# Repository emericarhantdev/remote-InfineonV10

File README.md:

# ECAD-TEMPLATE
Template for creating a new electronic design project. Automatically add gitignore and submodule library

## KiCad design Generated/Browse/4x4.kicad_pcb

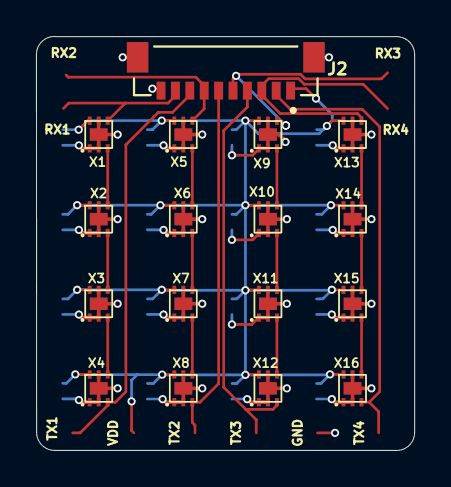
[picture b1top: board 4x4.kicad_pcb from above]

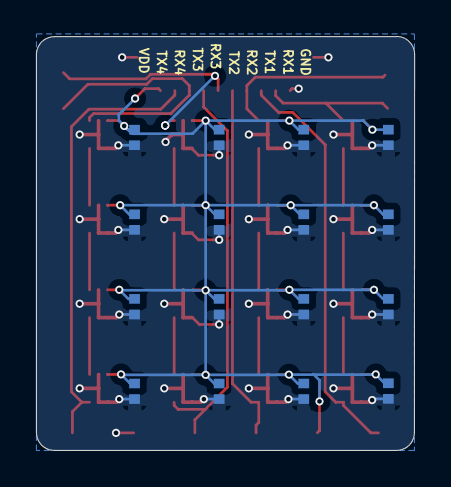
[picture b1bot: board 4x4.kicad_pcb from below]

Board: 2 copper layers, 21.0 x 23.0 mm, 33 parts (16 on the bottom side), 22 nets.

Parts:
CC_1, CC_2, CC_3, CC_4, CC_5, CC_6, CC_7, CC_8, CC_9, CC_10, CC_11, CC_12, CC_13, CC_14, CC_15, CC_16: C0402-CAPC1005X22N
J2: Amphenol-ICC_Minitek-08_10P
X1, X2, X3, X4, X5, X6, X7, X8, X9, X10, X11, X12, X13, X14, X15, X16: TLI493D-x4D7_R7_R1103_V3

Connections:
/Sensor Group/RX1: J2.9, X1.4 (TX)
/Sensor Group/RX2: J2.7, X5.4 (TX)
/Sensor Group/RX3: J2.5, X9.4 (TX)
/Sensor Group/RX4: J2.3, X13.4 (TX)
/Sensor Group/TX1: J2.8, X4.3 (RX)
/Sensor Group/TX2: J2.6, X8.3 (RX)
/Sensor Group/TX3: J2.4, X12.3 (RX)
/Sensor Group/TX4: J2.2, X16.3 (RX)
GND: CC_1.2, CC_2.2, CC_3.2, CC_4.2, CC_5.2, CC_6.2, CC_7.2, CC_8.2, CC_9.2, CC_10.2, CC_11.2, CC_12.2, CC_13.2, CC_14.2, CC_15.2, CC_16.2, J2.10, J2.S1 (SHIELD), J2.S2 (SHIELD__1), X1.1 (GND), X1.2 (NC), X1.5 (NC), X1.EP (NC), X2.1 (GND), X2.2 (NC), X2.5 (NC), X2.EP (NC), X3.1 (GND), X3.2 (NC), X3.5 (NC), X3.EP (NC), X4.1 (GND), X4.2 (NC), X4.5 (NC), X4.EP (NC), X5.1 (GND), X5.2 (NC), X5.5 (NC), X5.EP (NC), X6.1 (GND), X6.2 (NC), X6.5 (NC), X6.EP (NC), X7.1 (GND), X7.2 (NC), X7.5 (NC), X7.EP (NC), X8.1 (GND), X8.2 (NC), X8.5 (NC), X8.EP (NC), X9.1 (GND), X9.2 (NC), X9.5 (NC), X9.EP (NC), X10.1 (GND), X10.2 (NC), X10.5 (NC), X10.EP (NC), X11.1 (GND), X11.2 (NC), X11.5 (NC), X11.EP (NC), X12.1 (GND), X12.2 (NC), X12.5 (NC), X12.EP (NC), X13.1 (GND), X13.2 (NC), X13.5 (NC), X13.EP (NC), X14.1 (GND), X14.2 (NC), X14.5 (NC), X14.EP (NC), X15.1 (GND), X15.2 (NC), X15.5 (NC), X15.EP (NC), X16.1 (GND), X16.2 (NC), X16.5 (NC), X16.EP (NC)
unnamed: X1.3 (RX), X2.4 (TX)
unnamed: X2.3 (RX), X3.4 (TX)
unnamed: X3.3 (RX), X4.4 (TX)
unnamed: X5.3 (RX), X6.4 (TX)
unnamed: X6.3 (RX), X7.4 (TX)
unnamed: X7.3 (RX), X8.4 (TX)
unnamed: X10.3 (RX), X11.4 (TX)
unnamed: X9.3 (RX), X10.4 (TX)
unnamed: X11.3 (RX), X12.4 (TX)
unnamed: X13.3 (RX), X14.4 (TX)
unnamed: X14.3 (RX), X15.4 (TX)
unnamed: X15.3 (RX), X16.4 (TX)
VDD: CC_1.1, CC_2.1, CC_3.1, CC_4.1, CC_5.1, CC_6.1, CC_7.1, CC_8.1, CC_9.1, CC_10.1, CC_11.1, CC_12.1, CC_13.1, CC_14.1, CC_15.1, CC_16.1, J2.1, X1.6 (VDD), X2.6 (VDD), X3.6 (VDD), X4.6 (VDD), X5.6 (VDD), X6.6 (VDD), X7.6 (VDD), X8.6 (VDD), X9.6 (VDD), X10.6 (VDD), X11.6 (VDD), X12.6 (VDD), X13.6 (VDD), X14.6 (VDD), X15.6 (VDD), X16.6 (VDD)
